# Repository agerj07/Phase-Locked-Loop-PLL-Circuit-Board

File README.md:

# Phase-Locked-Loop-PLL-Circuit-Board
Phase Locked Loop(PLL) Circuit Board utilized in multiphoton microscopy

Utilized KiCAD to design and construct a PLL circuit board for tissue imaging using Arduino as an interface to the AD9544 IC chip.
Reduced lab costs by 78%

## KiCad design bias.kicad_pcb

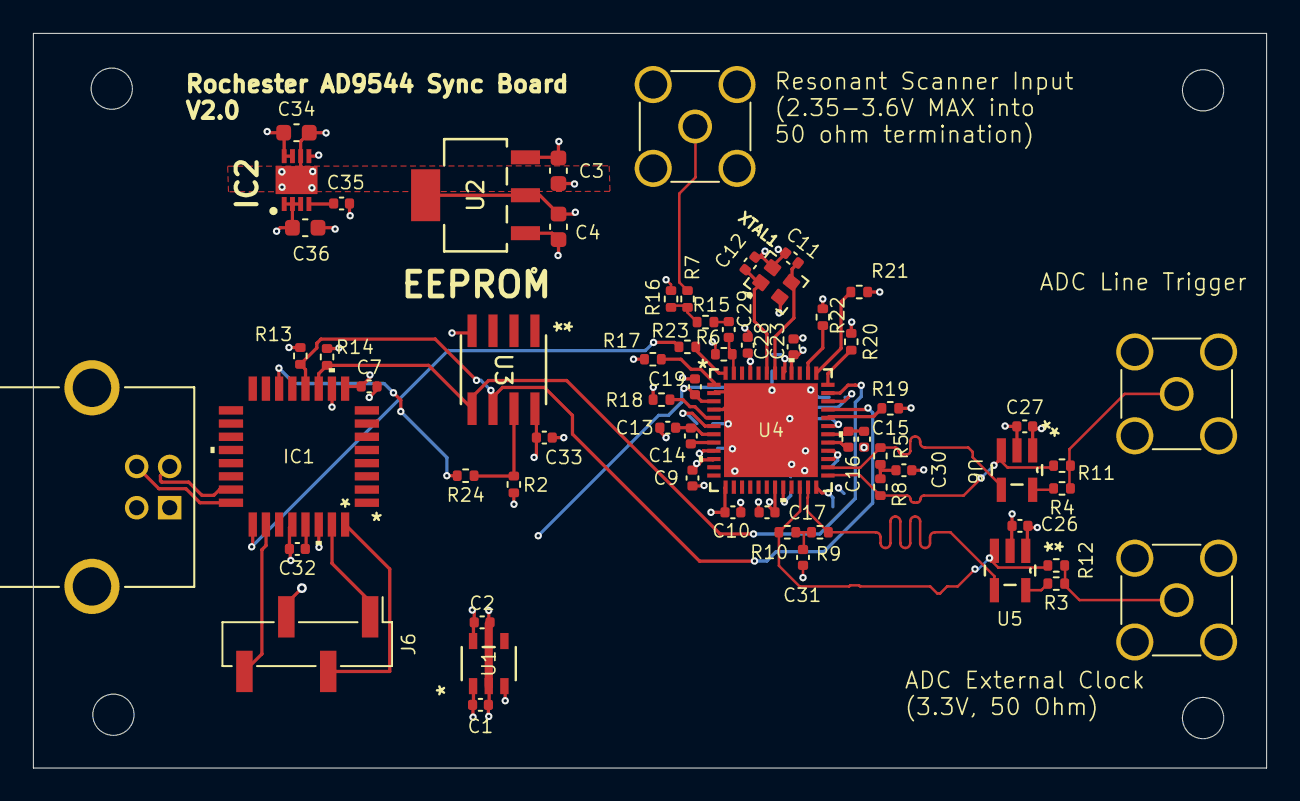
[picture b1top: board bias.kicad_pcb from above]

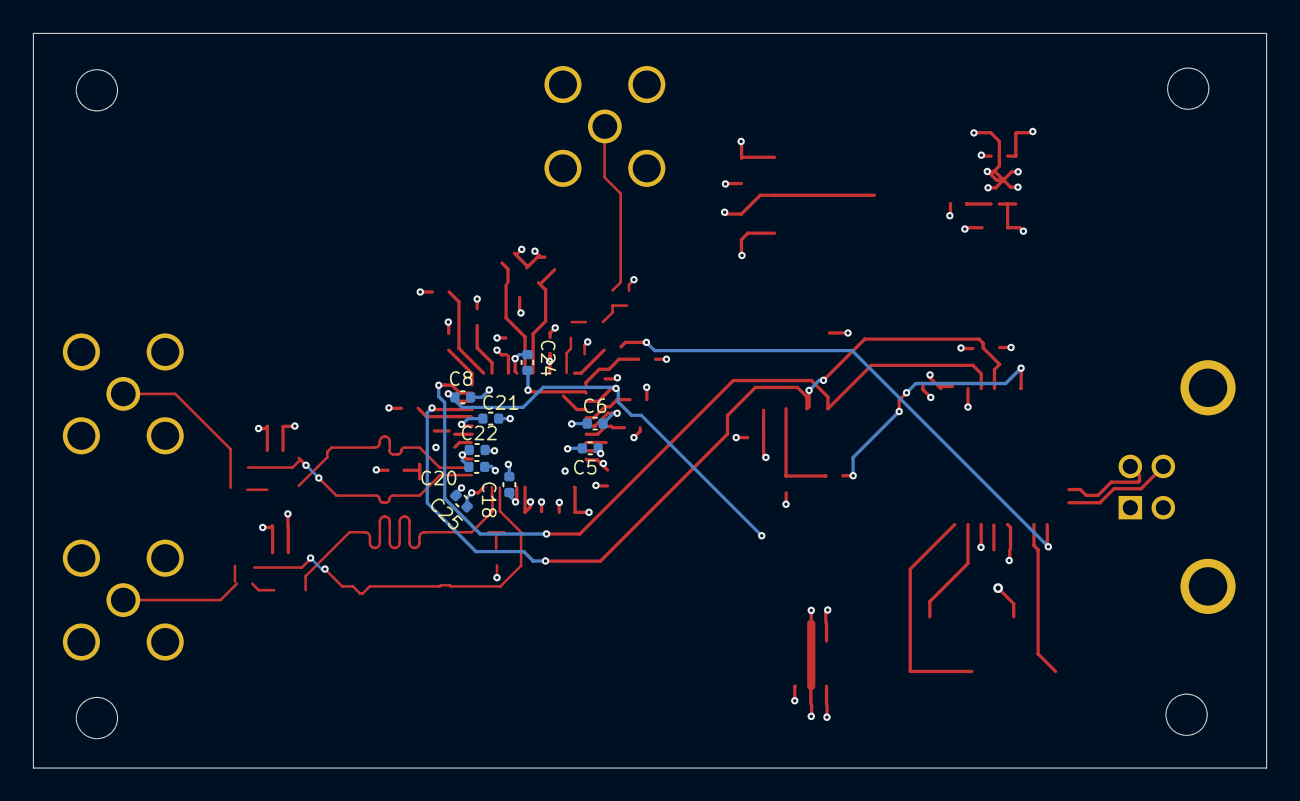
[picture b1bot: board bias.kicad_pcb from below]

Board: 4 copper layers, 74.8 x 44.5 mm, 77 parts (9 on the bottom side), 43 nets.

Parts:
C1, C2, C5, C6, C7, C8, C9, C10, C13, C15, C17, C18, C19, C20, C21, C22, C23, C24, C25, C26, C27, C28, C29, C30, C31, C32, C33: 1uF; C_0402_1005Metric
C3, C4, C34, C36: 22uF; C_0603_1608Metric
C11, C12: 15pF; C_0402_1005Metric
C14, C16: 3.9nF; C_0402_1005Metric
C35: 1nF; C_0402_1005Metric
H1, H2, H3, H4: MountingHole; MountingHole_2.5mm
IC1: ATSAMD21E18A-MUT; TQFP32_MC_MCH
IC2: ADM7171ACPZ-R7; SON50P300X300X80-9N-D
J1: USB1130-15-A_REVA; OST_USB-B1HSB6
J3, J4, J5: Conn_Coaxial; SMA_Amphenol_901-144_Vertical
J6: Conn_01x04; PinHeader_1x04_P2.54mm_Vertical_SMD_Pin1Left
R2, R13, R14, R17, R18, R19, R20, R21: 5.1k; R_0402_1005Metric
R3, R4: R_Small_US; R_0402_1005Metric
R5, R6, R8, R9, R10: 50; R_0402_1005Metric
R7, R15: 8.5; R_0402_1005Metric
R11, R12, R22, R23, R24: 0; R_0402_1005Metric
R16: 141.9; R_0402_1005Metric
U1: MIC5317-3.3YM5-TR; SOT-23-5_M5_MCH
U2: AZ1117CH-1.8TRG1; SOT-223_DIO
U3: 24AA16-I/SN; SOIC8-N_MC_MCH
U4: AD9544BCPZ; CP-48-13_ADI
U5, U6: SN65LVDS2DBVR; DBV5
XTAL1: NX2016SA-52MHZ-EXS00A-CS07103; OSCCC200X160X50N

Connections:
+1V8: C4.1, C5.1, C6.1, C9.1, C10.1, C17.1, C18.1, C20.1, C21.1, C22.1, C23.1, C24.1, C25.1, C28.1, C36.1, IC2.1 (VOUT_1), IC2.2 (VOUT_2), IC2.3 (SENSE), R20.1, R21.1, U2.2 (OUTPUT), U2.4 (EPAD), U4.6 (VDD), U4.9 (VDD), U4.10 (VDD), U4.13 (VDD), U4.19 (VDD), U4.20 (VDD), U4.24 (VDD), U4.27 (VDD), U4.28 (VDD), U4.31 (VDD), U4.40 (VDD), U4.41 (VDD), U4.45 (VDD)
+3V3: C2.1, C7.1, C8.1, C19.1, C26.2, C27.2, C33.1, IC1.9 (VDDANA), IC1.30 (VDDIN), R13.1, R14.1, U1.5 (VOUT), U3.8 (VCC), U4.3 (VDDIOA), U4.34 (VDDIOB), U5.1 (VCC), U6.1 (VCC)
+5V: C1.1, C3.1, C34.1, IC2.5 (EN), IC2.7 (VIN_1), IC2.8 (VIN_2), J1.1 (VCC), U1.1 (VIN), U1.3 (EN), U2.3 (INPUT)
/GPIO 1: R2.1, R24.1, U3.7 (WP)
/GPIO 2: IC1.25 (PA27), R23.1
/OUT1AN: R5.2, U4.26 (OUT1AN), U6.4 (B)
/OUT1AP: R8.1, R11.2, U4.25 (OUT1AP), U6.3 (A)
/OUT1BN: R9.2, U4.23 (OUT1BN), U5.4 (B)
/OUT1BP: R10.1, R12.2, U4.22 (OUT1BP), U5.3 (A)
/REFA: C29.2, R6.1, U4.47 (REFA)
/RESET: IC1.26 (~RESET), J6.4
/SCL: IC1.12 (PA09), R13.2, U3.6 (SERIAL_CLK), U4.33 (M1)
/SDA: IC1.11 (PA08), R14.2, U3.5 (SER_DATA_I/O), U4.35 (M2)
/SWCLK: IC1.31 (PA30), J6.1
/SWDIO: IC1.32 (PA31), J6.2
/USB_DN: IC1.23 (PA24), J1.2 (D-)
/USB_DP: IC1.24 (PA25), J1.3 (D+)
/XOA: C11.2, U4.42 (XOA), XTAL1.3
/XOB: C12.1, U4.43 (XOB), XTAL1.1
/out1: R4.2, U6.5 (R)
/out2: R3.2, U5.5 (R)
GND: C1.2, C2.2, C3.2, C4.2, C5.2, C6.2, C7.2, C8.2, C9.2, C10.2, C11.1, C12.2, C13.2, C15.2, C17.2, C18.2, C19.2, C20.2, C21.2, C22.2, C23.2, C24.2, C25.2, C26.1, C27.1, C28.2, C30.2, C31.2, C32.2, C33.2, C34.2, C35.1, C36.2, IC1.10 (GND_1), IC1.28 (GND_2), IC2.6 (GND), IC2.9 (EP), J1.4 (GND), J3.2 (Ext), J4.2 (Ext), J5.2 (Ext), J6.3, R2.2, R6.2, R16.1, R17.2, R18.2, R19.2, R22.1, U1.2 (GND), U2.1 (ADJ/GND), U3.4 (VSS), U4.2 (SCLK/SCL), U4.4 (SDIO/SDA), U4.49 (GND), U5.2 (GND), U6.2 (GND), XTAL1.2 (GND), XTAL1.4 (GND__1)
unnamed: C29.1, R15.1
unnamed: C30.1, R5.1, R8.2
unnamed: C31.1, R9.1, R10.2
unnamed: IC1.14 (PA11), R24.2
unnamed: C32.1, IC1.29 (VDDCORE)
unnamed: C35.2, IC2.4 (SS)
unnamed: J3.1 (In), R3.1, R12.1
unnamed: J4.1 (In), R4.1, R11.1
unnamed: J5.1 (In), R7.2
unnamed: R7.1, R15.2, R16.2
unnamed: R18.1, U4.5 (CSB/M6)
unnamed: C13.1, C14.1, U4.7 (LDO0)
unnamed: C15.1, C16.2, U4.30 (LDO1)
unnamed: C14.2, U4.8 (LF0)
unnamed: C16.1, U4.29 (LF1)
unnamed: R19.1, U4.32 (M0)
unnamed: R20.2, U4.36 (M3)
unnamed: R21.2, U4.37 (M4)
unnamed: R22.2, U4.38 (REFB)
unnamed: R23.2, U4.48 (RESETB)
unnamed: R17.1, U4.1 (SDO/M5)

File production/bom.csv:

Designator,Footprint,Quantity,Value,LCSC Part #
C1,0402,1,1uF,
C10,0402,1,1uF,
C11,0402,1,15pF,
C12,0402,1,15pF,
C13,0402,1,1uF,
C14,0402,1,3.9nF,
C15,0402,1,1uF,
C16,0402,1,3.9nF,
C17,0402,1,1uF,
C18,0402,1,1uF,
C19,0402,1,1uF,
C2,0402,1,1uF,
C20,0402,1,1uF,
C21,0402,1,1uF,
C22,0402,1,1uF,
C23,0402,1,1uF,
C24,0402,1,1uF,
C25,0402,1,1uF,
C26,0402,1,1uF,
C27,0402,1,1uF,
C28,0402,1,1uF,
C29,0402,1,1uF,
C3,0402,1,1uF,
C30,0402,1,1uF,
C31,0402,1,1uF,
C32,0402,1,1uF,
C33,0402,1,1uF,
C4,0402,1,1uF,
C5,0402,1,1uF,
C6,0402,1,1uF,
C7,0402,1,1uF,
C8,0402,1,1uF,
C9,0402,1,1uF,
"H1, H2, H3, H4",MountingHole_2.5mm,4,MountingHole,
IC1,TQFP32_MC_MCH,1,ATSAMD21E18A-MUT,
J1,OST_USB-B1HSB6,1,USB1130-15-A_REVA,
"J3, J4, J5",SMA_Amphenol_901-144_Vertical,3,Conn_Coaxial,
J6,PinHeader_1x04_P2.54mm_Vertical_SMD_Pin1Left,1,Conn_01x04,
R1,0402,1,0,
R10,0402,1,50,
R11,0402,1,0,
R12,0402,1,0,
R13,0402,1,5.1k,
R14,0402,1,5.1k,
R15,0402,1,8.5,
R16,0402,1,141.9,
R17,0402,1,5.1k,
R18,0402,1,5.1k,
R19,0402,1,5.1k,
R2,0402,1,1.1k,
R20,0402,1,5.1k,
R21,0402,1,5.1k,
R22,0402,1,0,
R23,0402,1,0,
R3,0402,1,R_Small_US,
R4,0402,1,R_Small_US,
R5,0402,1,50,
R6,0402,1,50,
R7,0402,1,8.5,
R8,0402,1,50,
R9,0402,1,50,
U1,SOT-23-5_M5_MCH,1,MIC5317-3.3YM5-TR,
U2,SOT-23-5_M5_MCH,1,MIC5317-1.8YM5-TR,
U3,SOIC8-N_MC_MCH,1,24AA16-I/SN,
U4,CP-48-13_ADI,1,AD9544BCPZ,
"U5, U6",DBV5,2,SN65LVDS2DBVR,
XTAL1,OSCCC200X160X50N,1,NX2016SA-52MHZ-EXS00A-CS07103,
